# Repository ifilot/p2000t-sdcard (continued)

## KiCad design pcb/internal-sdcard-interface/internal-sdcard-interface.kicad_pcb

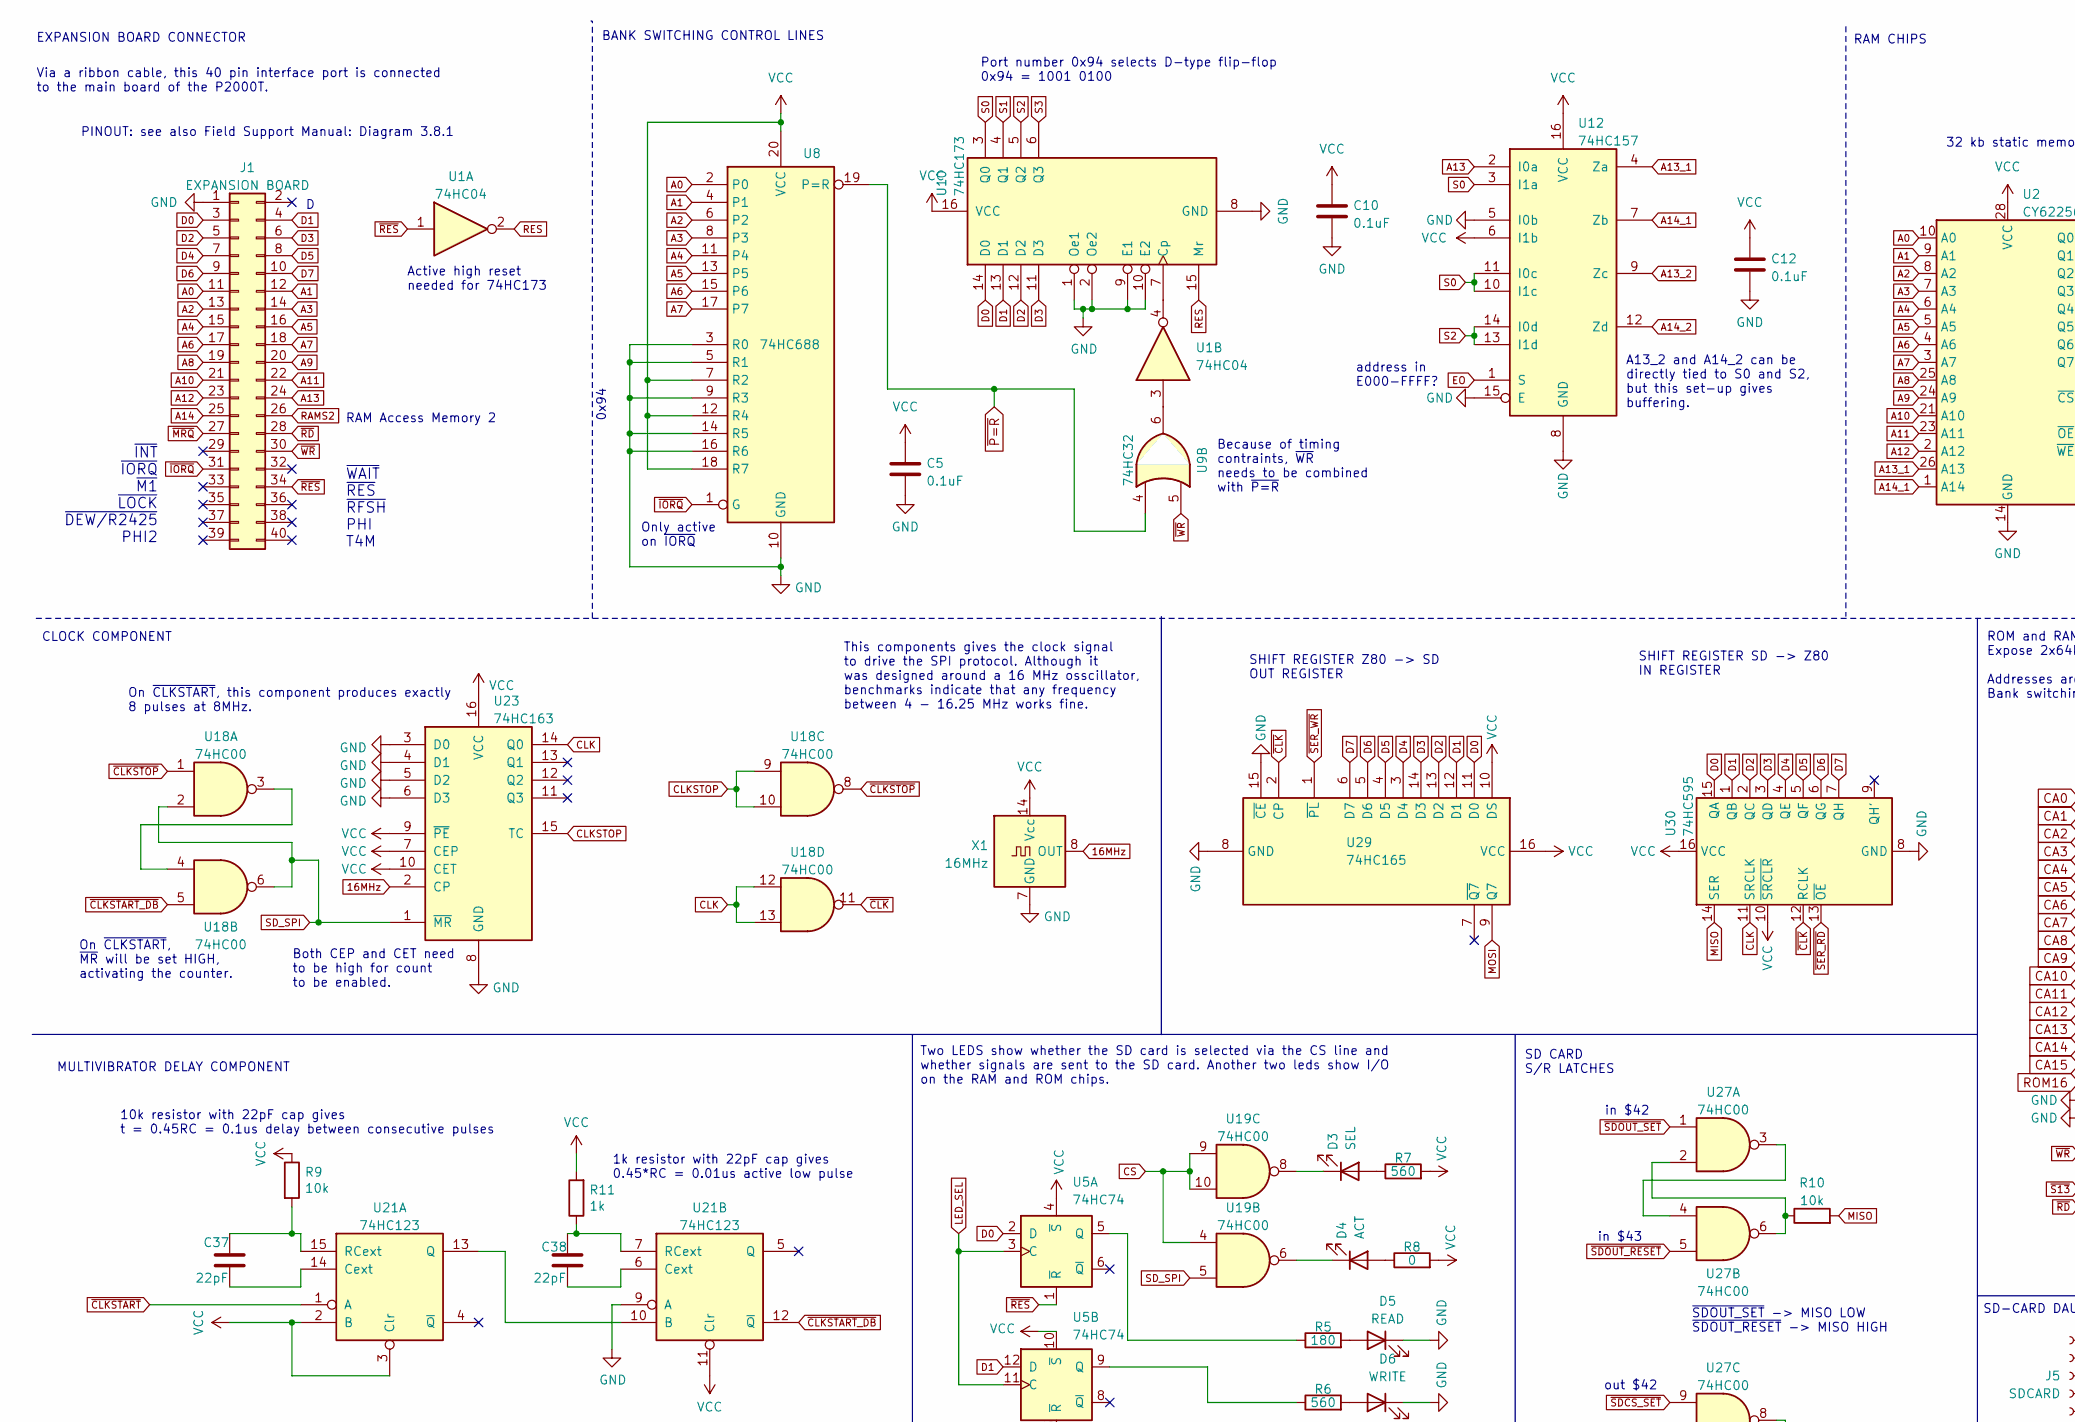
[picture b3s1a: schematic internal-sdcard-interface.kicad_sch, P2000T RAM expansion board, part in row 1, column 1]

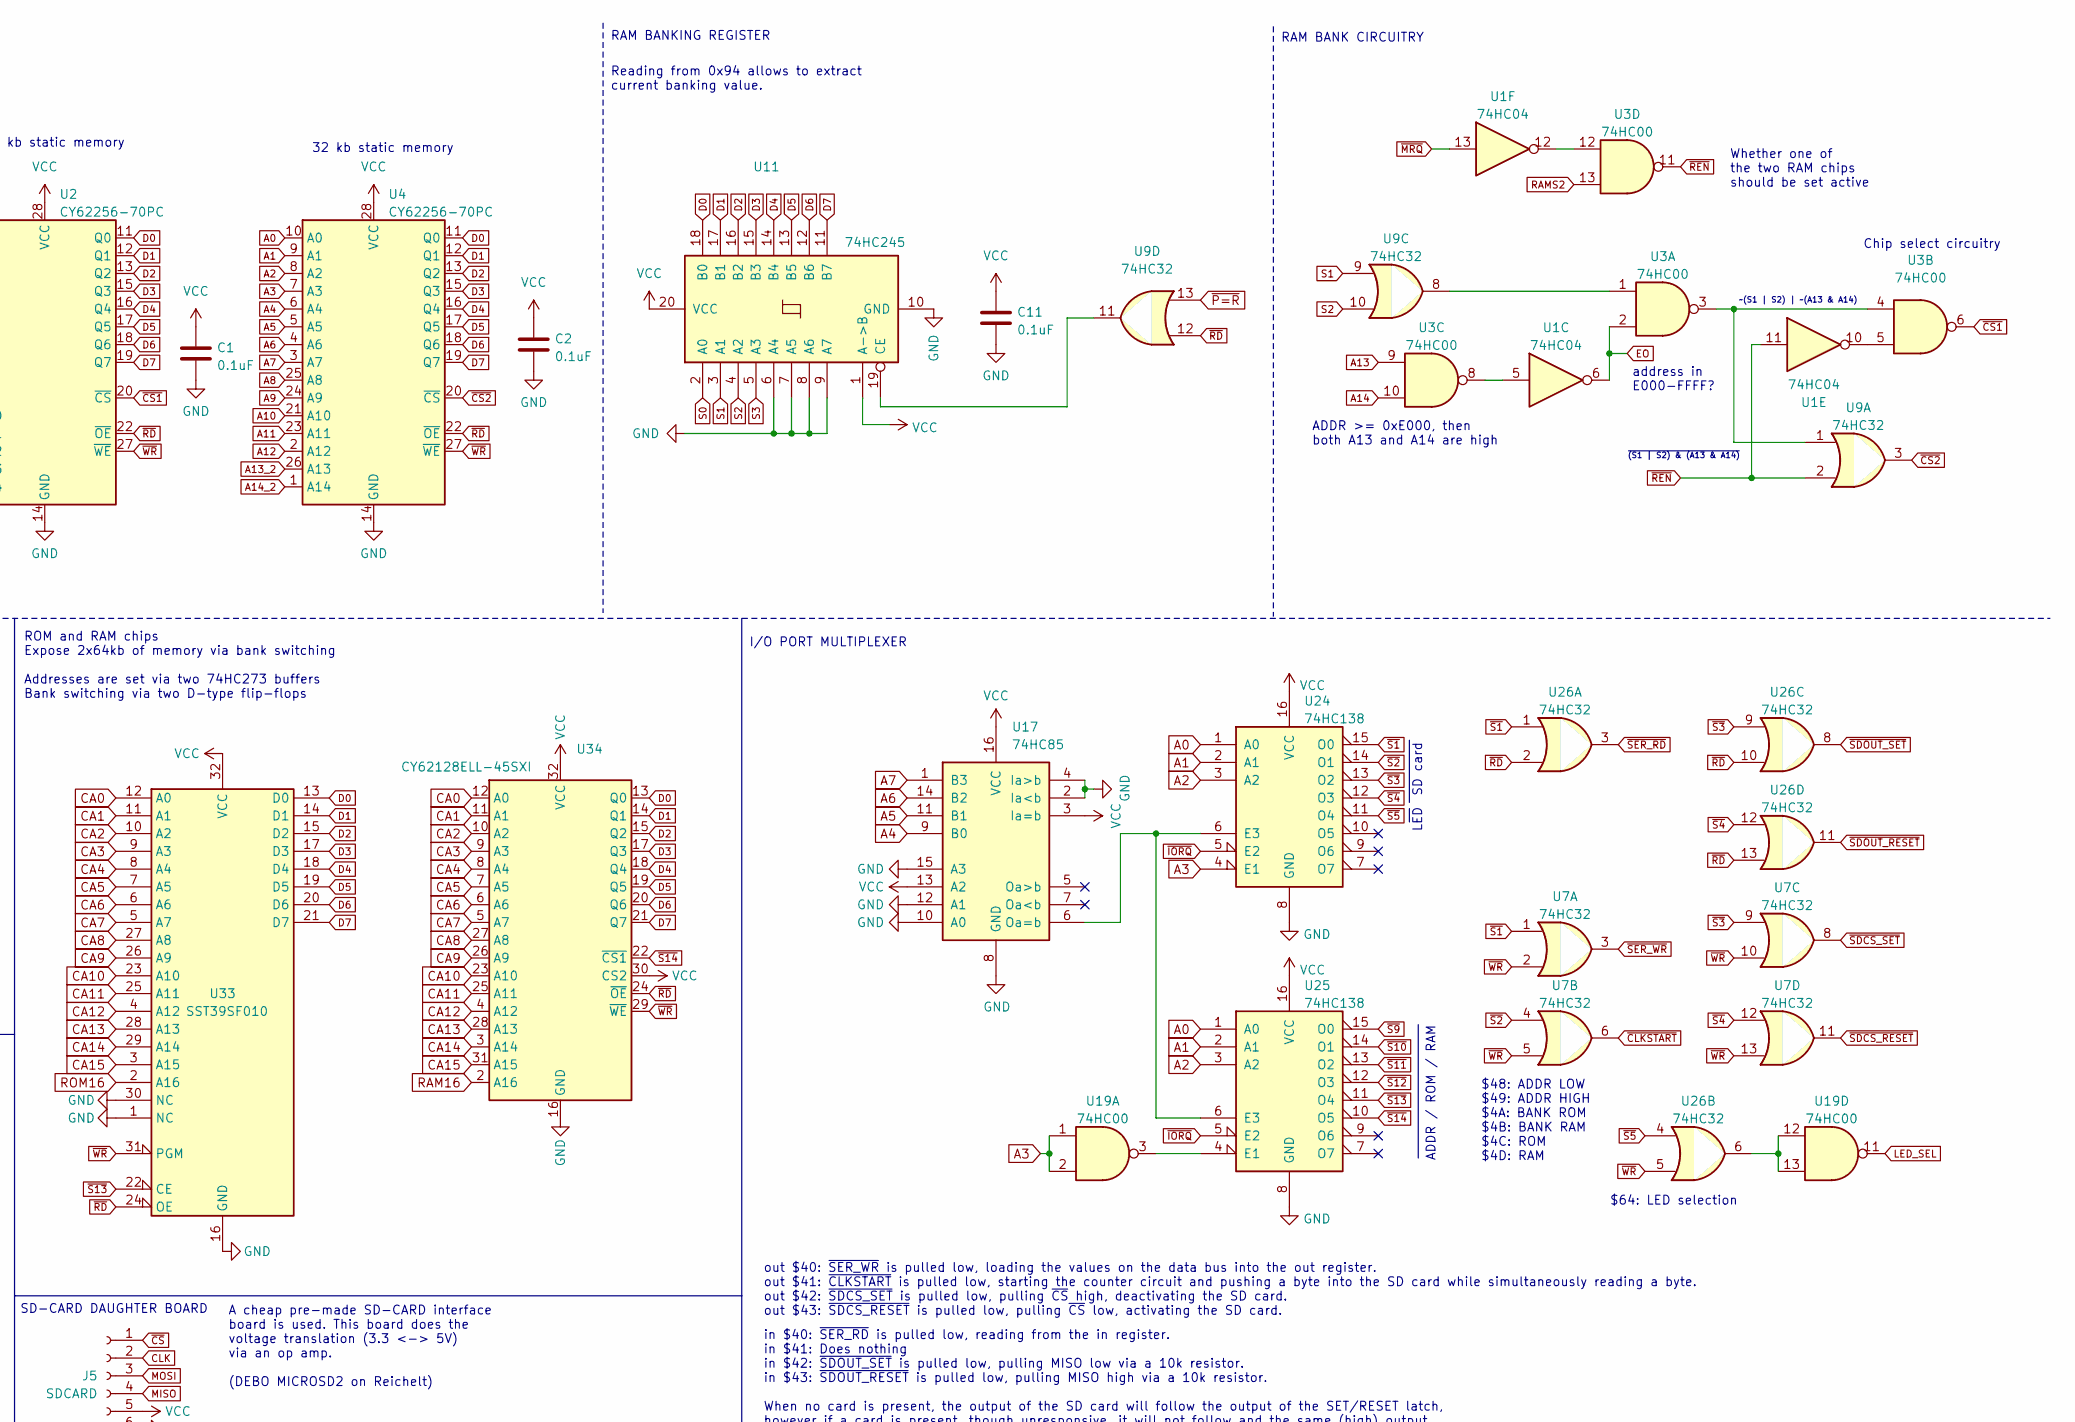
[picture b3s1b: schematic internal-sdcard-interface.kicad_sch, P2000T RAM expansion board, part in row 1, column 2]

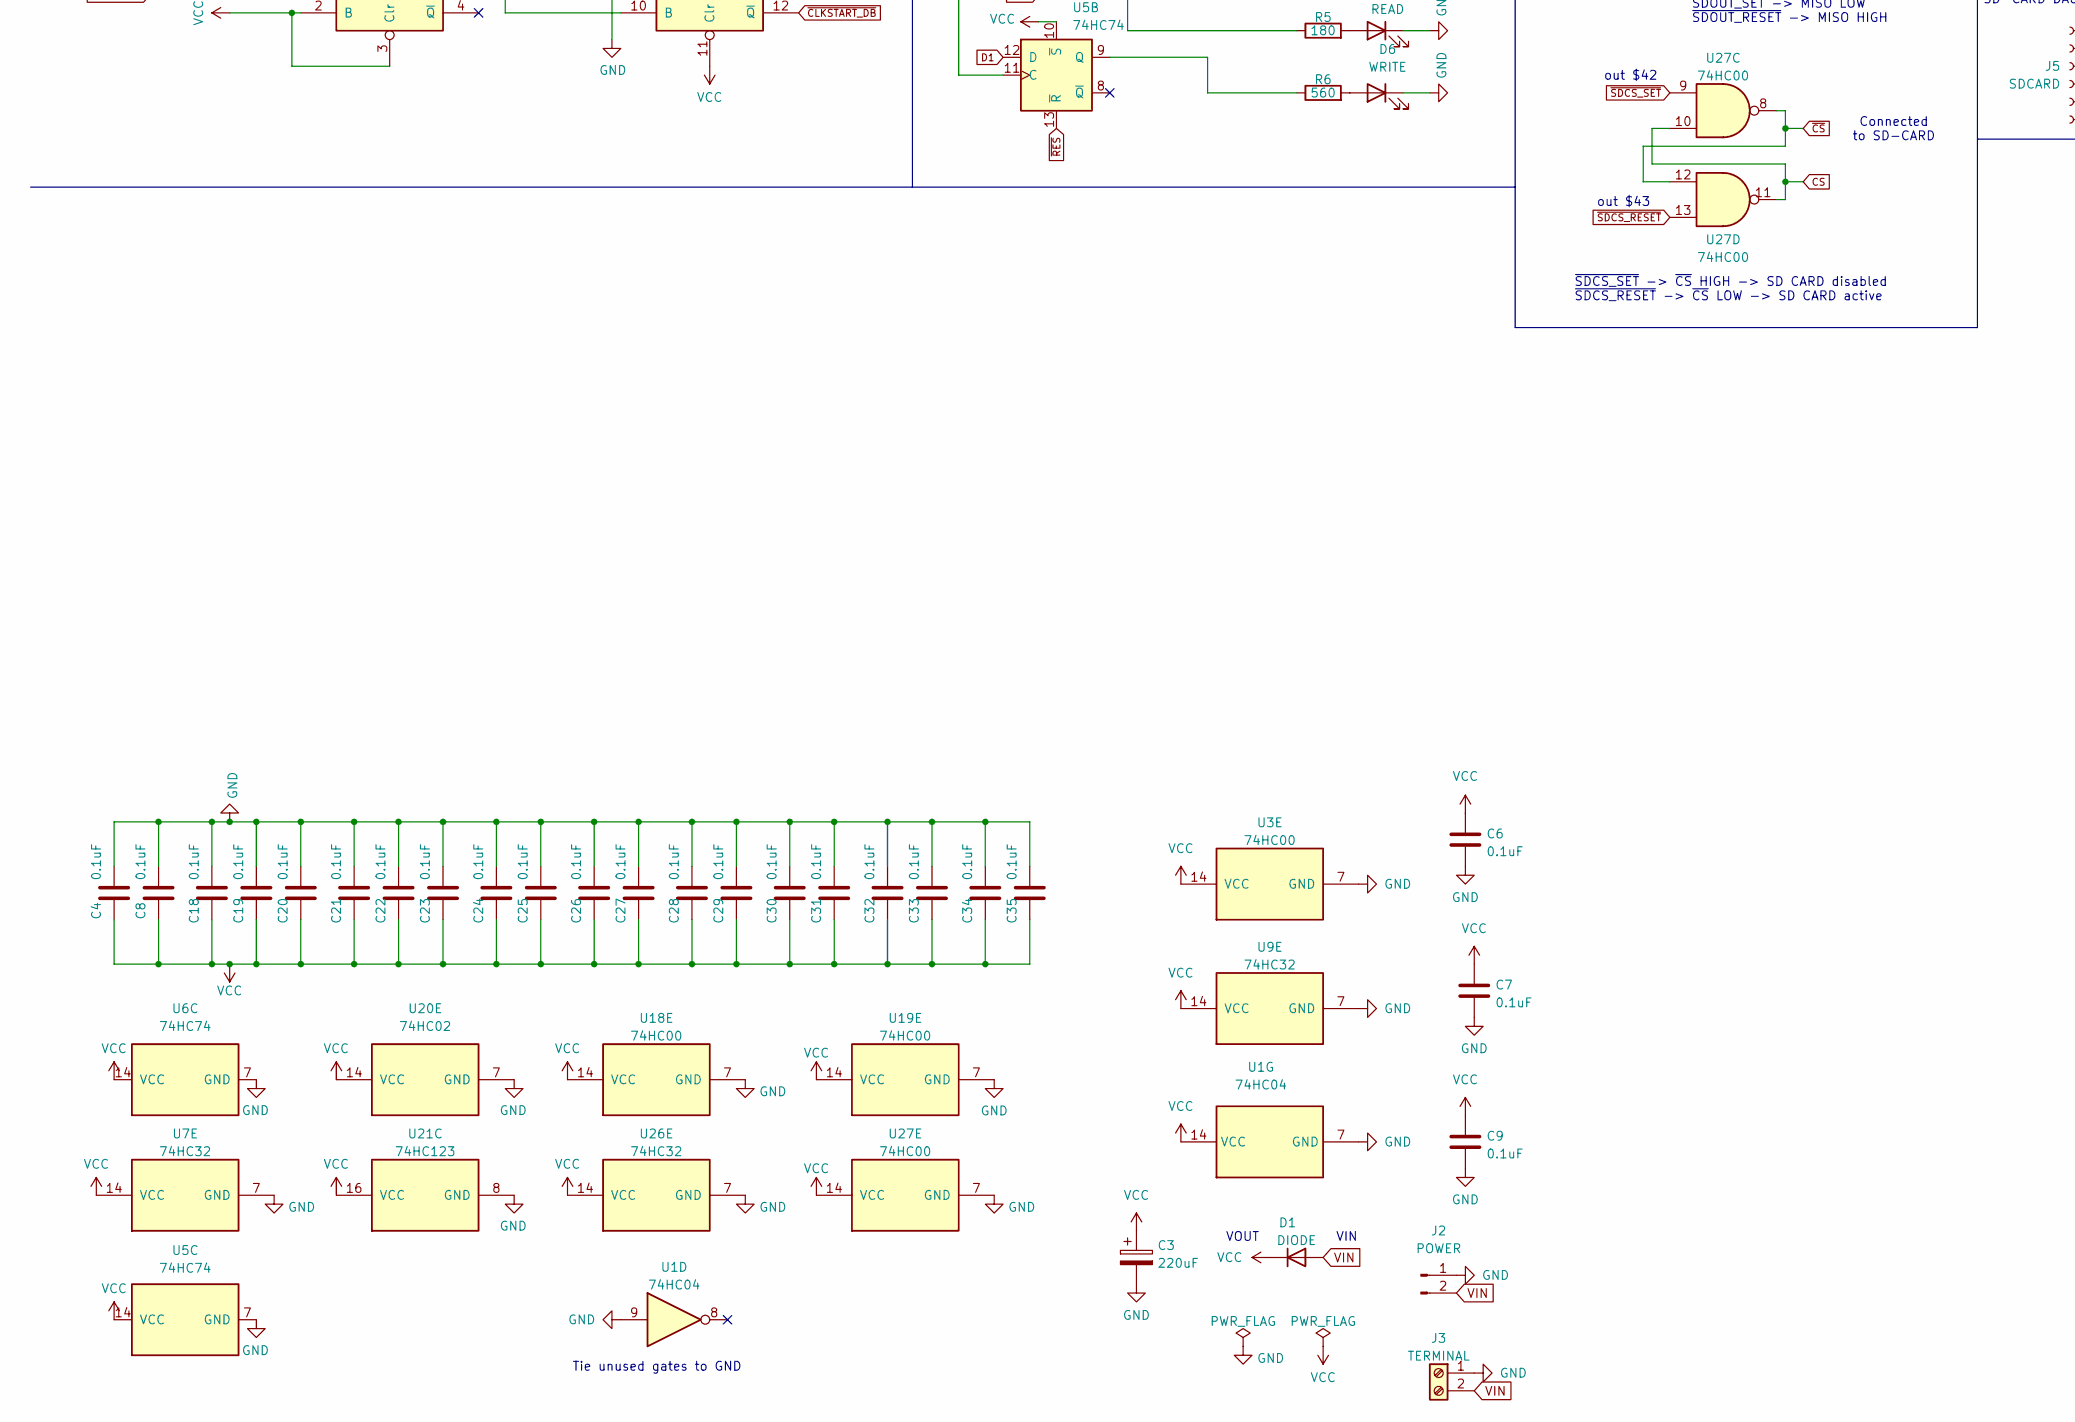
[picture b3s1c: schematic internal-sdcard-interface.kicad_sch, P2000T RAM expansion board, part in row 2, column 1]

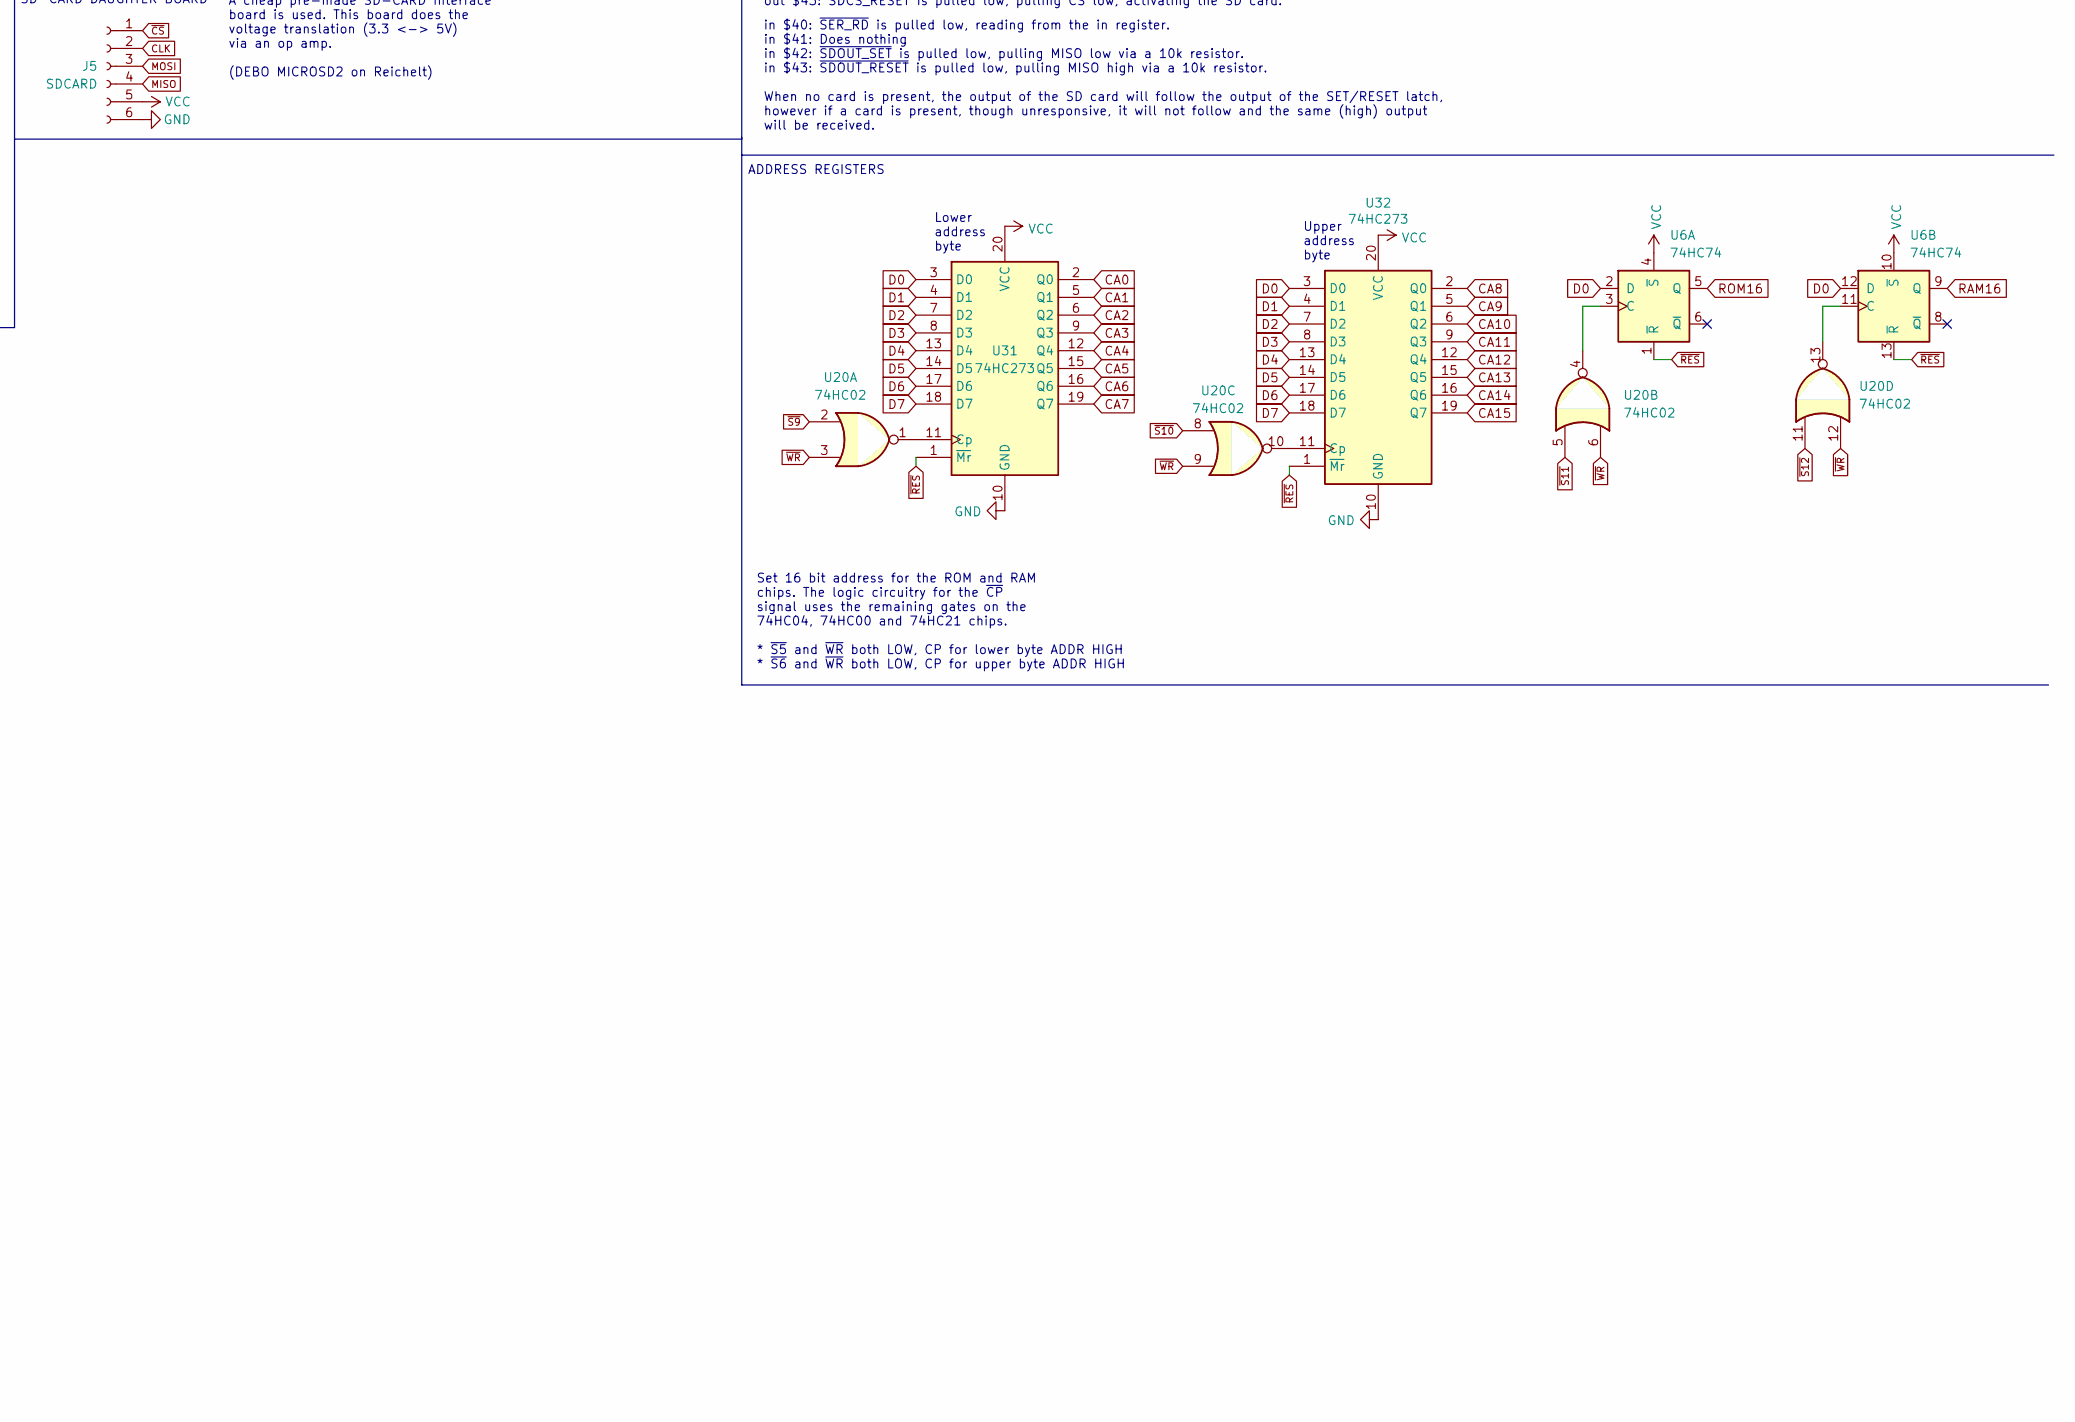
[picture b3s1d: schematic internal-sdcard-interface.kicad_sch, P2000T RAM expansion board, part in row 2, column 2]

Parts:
C1, C2, C5, C6, C7, C9, C10, C11, C12: 0.1uF; C_Disc_D5.0mm_W2.5mm_P5.00mm
C3: 220uF; CP_Radial_D6.3mm_P2.50mm
C4, C8, C18, C19, C20, C21, C22, C23, C24, C25, C26, C27, C28, C29, C30, C31, C32, C33, C34, C35: 0.1uF; C_Disc_D5.0mm_W2.5mm_P5.00mm; LCSC Part # C126469
C37, C38: 22pF; C_Disc_D5.0mm_W2.5mm_P5.00mm; LCSC Part # C525286
D1: DIODE; D_DO-35_SOD27_P7.62mm_Horizontal
D3: SEL; LED_D5.0mm
D4: ACT; LED_D5.0mm
D5: READ; LED_D5.0mm
D6: WRITE; LED_D5.0mm
J1: EXPANSION BOARD; IDC-Header_2x20_P2.54mm_Vertical
J2: POWER; PinHeader_1x02_P2.54mm_Vertical
J3: TERMINAL; TerminalBlock_bornier-2_P5.08mm
J5: SDCARD; sdcard-socket
R5: 180; R_Axial_DIN0207_L6.3mm_D2.5mm_P7.62mm_Horizontal; LCSC Part # C429158
R6, R7: 560; R_Axial_DIN0207_L6.3mm_D2.5mm_P7.62mm_Horizontal; LCSC Part # C429158
R8: 0; R_Axial_DIN0207_L6.3mm_D2.5mm_P7.62mm_Horizontal; LCSC Part # C431818
R9, R10: 10k; R_Axial_DIN0207_L6.3mm_D2.5mm_P7.62mm_Horizontal; LCSC Part # C5159708
R11: 1k; R_Axial_DIN0207_L6.3mm_D2.5mm_P7.62mm_Horizontal; LCSC Part # C5123594
U1: 74HC04; DIP-14_W7.62mm_Socket
U2, U4: CY62256-70PC; DIP-28_W15.24mm_Socket
U3: 74HC00; DIP-14_W7.62mm_Socket
U5, U6: 74HC74; DIP-14_W7.62mm_Socket; LCSC Part # C27597
U7, U26: 74HC32; DIP-14_W7.62mm_Socket; LCSC Part # C5632
U8: 74HC688; DIP-20_W7.62mm_Socket
U9: 74HC32; DIP-14_W7.62mm_Socket
U10: 74HC173; DIP-16_W7.62mm_Socket
U11: 74HC245; DIP-20_W7.62mm_Socket
U12: 74HC157; DIP-16_W7.62mm_Socket
U17: 74HC85; DIP-16_W7.62mm_Socket; LCSC Part # C5953
U18, U19, U27: 74HC00; DIP-14_W7.62mm_Socket; LCSC Part # C699445
U20: 74HC02; DIP-14_W7.62mm_Socket; LCSC Part # C5588
U21: 74HC123; DIP-16_W7.62mm_Socket; LCSC Part # C5597
U23: 74HC163; DIP-16_W7.62mm_Socket; LCSC Part # C338758
U24, U25: 74HC138; DIP-16_W7.62mm_Socket; LCSC Part # C5602
U29: 74HC165; DIP-16_W7.62mm_Socket; LCSC Part # C5613
U30: 74HC595; DIP-16_W7.62mm_Socket; LCSC Part # C5947
U31, U32: 74HC273; DIP-20_W7.62mm_Socket; LCSC Part # C131486
U33: SST39SF010; PLCC-32_THT-Socket
U34: CY62128ELL-45SXI; SSOP-32_11.305x20.495mm_P1.27mm; LCSC Part # C2840304
X1: 16MHz; Oscillator_DIP-14

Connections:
16MHz: U23.2 (CP), X1.8 (OUT)
A0: J1.11, U2.10 (A0), U4.10 (A0), U8.2 (P0), U24.1 (A0), U25.1 (A0)
A1: J1.12, U2.9 (A1), U4.9 (A1), U8.4 (P1), U24.2 (A1), U25.2 (A1)
A2: J1.13, U2.8 (A2), U4.8 (A2), U8.6 (P2), U24.3 (A2), U25.3 (A2)
A3: J1.14, U2.7 (A3), U4.7 (A3), U8.8 (P3), U19.1, U19.2, U24.4 (E1)
A4: J1.15, U2.6 (A4), U4.6 (A4), U8.11 (P4), U17.9 (B0)
A5: J1.16, U2.5 (A5), U4.5 (A5), U8.13 (P5), U17.11 (B1)
A6: J1.17, U2.4 (A6), U4.4 (A6), U8.15 (P6), U17.14 (B2)
A7: J1.18, U2.3 (A7), U4.3 (A7), U8.17 (P7), U17.1 (B3)
A8: J1.19, U2.25 (A8), U4.25 (A8)
A9: J1.20, U2.24 (A9), U4.24 (A9)
A10: J1.21, U2.21 (A10), U4.21 (A10)
A11: J1.22, U2.23 (A11), U4.23 (A11)
A12: J1.23, U2.2 (A12), U4.2 (A12)
A13: J1.24, U3.9, U12.2 (I0a)
A13_1: U2.26 (A13), U12.4 (Za)
A13_2: U4.26 (A13), U12.9 (Zc)
A14: J1.25, U3.10
A14_1: U2.1 (A14), U12.7 (Zb)
A14_2: U4.1 (A14), U12.12 (Zd)
CA0: U31.2 (Q0), U33.12 (A0), U34.12 (A0)
CA1: U31.5 (Q1), U33.11 (A1), U34.11 (A1)
CA2: U31.6 (Q2), U33.10 (A2), U34.10 (A2)
CA3: U31.9 (Q3), U33.9 (A3), U34.9 (A3)
CA4: U31.12 (Q4), U33.8 (A4), U34.8 (A4)
CA5: U31.15 (Q5), U33.7 (A5), U34.7 (A5)
CA6: U31.16 (Q6), U33.6 (A6), U34.6 (A6)
CA7: U31.19 (Q7), U33.5 (A7), U34.5 (A7)
CA8: U32.2 (Q0), U33.27 (A8), U34.27 (A8)
CA9: U32.5 (Q1), U33.26 (A9), U34.26 (A9)
CA10: U32.6 (Q2), U33.23 (A10), U34.23 (A10)
CA11: U32.9 (Q3), U33.25 (A11), U34.25 (A11)
CA12: U32.12 (Q4), U33.4 (A12), U34.4 (A12)
CA13: U32.15 (Q5), U33.28 (A13), U34.28 (A13)
CA14: U32.16 (Q6), U33.29 (A14), U34.3 (A14)
CA15: U32.19 (Q7), U33.3 (A15), U34.31 (A15)
CLK: J5.2, U18.12, U18.13, U23.14 (Q0), U30.11 (SRCLK)
CLKSTOP: U18.9, U18.10, U23.15 (TC)
CS: U19.4, U19.9, U19.10, U27.10, U27.11
D0: J1.3, U2.11 (Q0), U4.11 (Q0), U5.2 (D), U6.2 (D), U6.12 (D), U10.14 (D0), U11.18 (B0), U29.11 (D0), U30.15 (QA), U31.3 (D0), U32.3 (D0), U33.13 (D0), U34.13 (Q0)
D1: J1.4, U2.12 (Q1), U4.12 (Q1), U5.12 (D), U10.13 (D1), U11.17 (B1), U29.12 (D1), U30.1 (QB), U31.4 (D1), U32.4 (D1), U33.14 (D1), U34.14 (Q1)
D2: J1.5, U2.13 (Q2), U4.13 (Q2), U10.12 (D2), U11.16 (B2), U29.13 (D2), U30.2 (QC), U31.7 (D2), U32.7 (D2), U33.15 (D2), U34.15 (Q2)
D3: J1.6, U2.15 (Q3), U4.15 (Q3), U10.11 (D3), U11.15 (B3), U29.14 (D3), U30.3 (QD), U31.8 (D3), U32.8 (D3), U33.17 (D3), U34.17 (Q3)
D4: J1.7, U2.16 (Q4), U4.16 (Q4), U11.14 (B4), U29.3 (D4), U30.4 (QE), U31.13 (D4), U32.13 (D4), U33.18 (D4), U34.18 (Q4)
D5: J1.8, U2.17 (Q5), U4.17 (Q5), U11.13 (B5), U29.4 (D5), U30.5 (QF), U31.14 (D5), U32.14 (D5), U33.19 (D5), U34.19 (Q5)
D6: J1.9, U2.18 (Q6), U4.18 (Q6), U11.12 (B6), U29.5 (D6), U30.6 (QG), U31.17 (D6), U32.17 (D6), U33.20 (D6), U34.20 (Q6)
D7: J1.10, U2.19 (Q7), U4.19 (Q7), U11.11 (B7), U29.6 (D7), U30.7 (QH), U31.18 (D7), U32.18 (D7), U33.21 (D7), U34.21 (Q7)
EO: U1.6, U3.2, U12.1 (S)
GND: C1.2, C2.2, C3.2, C4.2, C5.2, C6.2, C7.2, C8.2, C9.2, C10.2, C11.2, C12.2, C18.2, C19.2, C20.2, C21.2, C22.2, C23.2, C24.2, C25.2, C26.2, C27.2, C28.2, C29.2, C30.2, C31.2, C32.2, C33.2, C34.2, C35.2, D5.1 (K), D6.1 (K), J1.1, J2.1, J3.1, J5.6, U1.7 (GND), U1.9, U2.14 (GND), U3.7 (GND), U4.14 (GND), U5.7 (GND), U6.7 (GND), U7.7 (GND), U8.3 (R0), U8.5 (R1), U8.9 (R3), U8.10 (GND), U8.14 (R5), U8.16 (R6), U9.7 (GND), U10.1 (Oe1), U10.2 (Oe2), U10.8 (GND), U10.9 (E1), U10.10 (E2), U11.6 (A4), U11.7 (A5), U11.8 (A6), U11.9 (A7), U11.10 (GND), U12.5 (I0b), U12.8 (GND), U12.15 (E), U17.2 (Ia<b), U17.4 (Ia>b), U17.8 (GND), U17.10 (A0), U17.12 (A1), U17.15 (A3), U18.7 (GND), U19.7 (GND), U20.7 (GND), U21.8 (GND), U21.9 (A), U23.3 (D0), U23.4 (D1), U23.5 (D2), U23.6 (D3), U23.8 (GND), U24.8 (GND), U25.8 (GND), U26.7 (GND), U27.7 (GND), U29.8 (GND), U29.15 (~CE), U30.8 (GND), U31.10 (GND), U32.10 (GND), U33.1 (NC), U33.16 (GND), U33.30 (NC), U34.16 (GND), X1.7 (GND)
LED_SEL: U5.3 (C), U5.11 (C), U19.11
MISO: J5.4, R10.2, U30.14 (SER)
MOSI: J5.3, U29.9 (Q7)
unnamed: D3.2 (A), R7.1
unnamed: D3.1 (K), U19.8
unnamed: D4.2 (A), R8.1
unnamed: D4.1 (K), U19.6
unnamed: D5.2 (A), R5.2
unnamed: D6.2 (A), R6.2
unnamed: R10.1, U27.2, U27.6
unnamed: U1.3, U9.6
unnamed: U1.5, U3.8
unnamed: U1.10, U3.5
unnamed: U1.12, U3.12
unnamed: U3.1, U9.8
unnamed: U3.3, U3.4, U9.1
unnamed: R5.1, U5.5 (Q)
unnamed: R6.1, U5.9 (Q)
unnamed: U6.3 (C), U20.4
unnamed: U6.11 (C), U20.13
unnamed: U1.4, U10.7 (Cp)
unnamed: U9.11, U11.19 (CE)
unnamed: U17.6 (Oa=b), U24.6 (E3), U25.6 (E3)
unnamed: U18.3, U18.4
unnamed: U19.12, U19.13, U26.6
unnamed: C37.1, U21.14 (Cext)
unnamed: U21.10 (B), U21.13 (Q)
unnamed: C37.2, R9.2, U21.15 (RCext)
unnamed: C38.1, U21.6 (Cext)
unnamed: C38.2, R11.1, U21.7 (RCext)
unnamed: U19.3, U25.4 (E1)
unnamed: U27.3, U27.4
unnamed: U20.1, U31.11 (Cp)
unnamed: U20.10, U32.11 (Cp)
RAM16: U6.9 (Q), U34.2 (A16)
RAMS2: J1.26, U3.13
RES: U1.2, U10.15 (Mr)
ROM16: U6.5 (Q), U33.2 (A16)
S0: U10.3 (Q0), U11.2 (A0), U12.3 (I1a), U12.10 (I1c), U12.11 (I0c)
S1: U9.9, U10.4 (Q1), U11.3 (A1)
S2: U9.10, U10.5 (Q2), U11.4 (A2), U12.13 (I1d), U12.14 (I0d)
S3: U10.6 (Q3), U11.5 (A3)
SD_SPI: U18.2, U18.6, U19.5, U23.1 (~MR)
VCC: C1.1, C2.1, C3.1, C4.1, C5.1, C6.1, C7.1, C8.1, C9.1, C10.1, C11.1, C12.1, C18.1, C19.1, C20.1, C21.1, C22.1, C23.1, C24.1, C25.1, C26.1, C27.1, C28.1, C29.1, C30.1, C31.1, C32.1, C33.1, C34.1, C35.1, D1.1 (K), J5.5, R7.2, R8.2, R9.1, R11.2, U1.14 (VCC), U2.28 (VCC), U3.14 (VCC), U4.28 (VCC), U5.4 (~S), U5.10 (~S), U5.14 (VCC), U6.4 (~S), U6.10 (~S), U6.14 (VCC), U7.14 (VCC), U8.7 (R2), U8.12 (R4), U8.18 (R7), U8.20 (VCC), U9.14 (VCC), U10.16 (VCC), U11.1 (A->B), U11.20 (VCC), U12.6 (I1b), U12.16 (VCC), U17.3 (Ia=b), U17.13 (A2), U17.16 (VCC), U18.14 (VCC), U19.14 (VCC), U20.14 (VCC), U21.2 (B), U21.3 (Clr), U21.11 (Clr), U21.16 (VCC), U23.7 (CEP), U23.9 (~PE), U23.10 (CET), U23.16 (VCC), U24.16 (VCC), U25.16 (VCC), U26.14 (VCC), U27.14 (VCC), U29.10 (DS), U29.16 (VCC), U30.10 (~SRCLR), U30.16 (VCC), U31.20 (VCC), U32.20 (VCC), U33.32 (VCC), U34.30 (CS2), U34.32 (VCC), X1.14 (Vcc)
VIN: D1.2 (A), J2.2, J3.2
~CLKSTART_DB: U18.5, U21.12 (~Q)
~CLKSTART: U7.6, U21.1 (A)
~CLKSTOP: U18.1, U18.8
~CLK: U18.11, U29.2 (CP), U30.12 (RCLK)
~CS1: U2.20 (~CS), U3.6
~CS2: U4.20 (~CS), U9.3
~CS: J5.1, U27.8, U27.12
~IORQ: J1.31, U8.1 (G), U24.5 (E2), U25.5 (E2)
~MRQ: J1.27, U1.13
~P=R: U8.19 (P=R), U9.4, U9.13
~RD: J1.28, U2.22 (~OE), U4.22 (~OE), U9.12, U26.2, U26.10, U26.13, U33.24 (OE), U34.24 (~OE)
~REN: U1.11, U3.11, U9.2
~RES: J1.34, U1.1, U5.1 (~R), U5.13 (~R), U6.1 (~R), U6.13 (~R), U31.1 (~Mr), U32.1 (~Mr)
~S1: U7.1, U24.15 (O0), U26.1
~S2: U7.4, U24.14 (O1)
~S3: U7.9, U24.13 (O2), U26.9
~S4: U7.12, U24.12 (O3), U26.12
~S5: U24.11 (O4), U26.4
~S9: U20.2, U25.15 (O0)
~S10: U20.8, U25.14 (O1)
~S11: U20.5, U25.13 (O2)
~S12: U20.11, U25.12 (O3)
~S13: U25.11 (O4), U33.22 (CE)
~S14: U25.10 (O5), U34.22 (~CS1)
~SDCS_RESET: U7.11, U27.13
~SDCS_SET: U7.8, U27.9
~SDOUT_RESET: U26.11, U27.5
~SDOUT_SET: U26.8, U27.1
~SER_RD: U26.3, U30.13 (~OE)
~SER_WR: U7.3, U29.1 (~PL)
~WR: J1.30, U2.27 (~WE), U4.27 (~WE), U7.2, U7.5, U7.10, U7.13, U9.5, U20.3, U20.6, U20.9, U20.12, U26.5, U33.31 (PGM), U34.29 (~WE)

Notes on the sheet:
Lower address byte
SD CARD S/R LATCHES
Upper address byte
Reading from 0x94 allows to extract current banking value.
Via a ribbon cable, this 40 pin interface port is connected to the main board of the P2000T.
32 kb static memory
EXPANSION BOARD CONNECTOR
RAM Access Memory 2
1k resistor with 22pF cap gives 0.45*RC = 0.01us active low pulse
Whether one of the two RAM chips should be set active
Two LEDS show whether the SD card is selected via the CS line and whether signals are sent to the SD card. Another two leds show I/O on the RAM and ROM chips.
This components gives the clock signal to drive the SPI protocol. Although it was designed around a 16 MHz osscillator, benchmarks indicate that any frequency between 4 - 16.25 MHz works fine.
out $40: ~{SER_WR} is pulled low, loading the values on the data bus into the out register. out $41: ~{CLKSTART} is pulled low, starting the counter circuit and pushing a byte into the SD card while simultaneously reading a byte. out $42: ~{SDCS_SET} is pulled low, pulling ~{CS} high, deactivating 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
A cheap pre-made SD-CARD interface board is used. This board does the voltage translation (3.3 <-> 5V) via an op amp. (DEBO MICROSD2 on Reichelt)
0x94
~{INT} ~{IORQ} ~{M1} ~{LOCK} ~{DEW/R2425} PHI2
ROM and RAM chips Expose 2x64kb of memory via bank switching Addresses are set via two 74HC273 buffers Bank switching via two D-type flip-flops
~{SDCS_SET} -> ~{CS} HIGH -> SD CARD disabled ~{SDCS_RESET} -> ~{CS} LOW -> SD CARD active
out $42
RAM BANKING REGISTER
I/O PORT MULTIPLEXER
~{(S1 | S2) & (A13 & A14)}
~{SDOUT_SET} -> MISO LOW ~{SDOUT_RESET} -> MISO HIGH
Tie unused gates to GND
SD card
RAM BANK CIRCUITRY
On ~{CLKSTART}, this component produces exactly 8 pulses at 8MHz.
Connected to SD-CARD
Active high reset needed for 74HC173
Only active on ~{IORQ}
Because of timing contraints, ~{WR} needs to be combined with ~{P=R}
address in E000-FFFF?
out $43
ADDR / ROM / RAM
10k resistor with 22pF cap gives t = 0.45RC = 0.1us delay between consecutive pulses
Both CEP and CET need to be high for count to be enabled.
SHIFT REGISTER SD -> Z80 IN REGISTER
On ~{CLKSTART}, ~{MR} will be set HIGH, activating the counter.
ADDR >= 0xE000, then both A13 and A14 are high
MULTIVIBRATOR DELAY COMPONENT

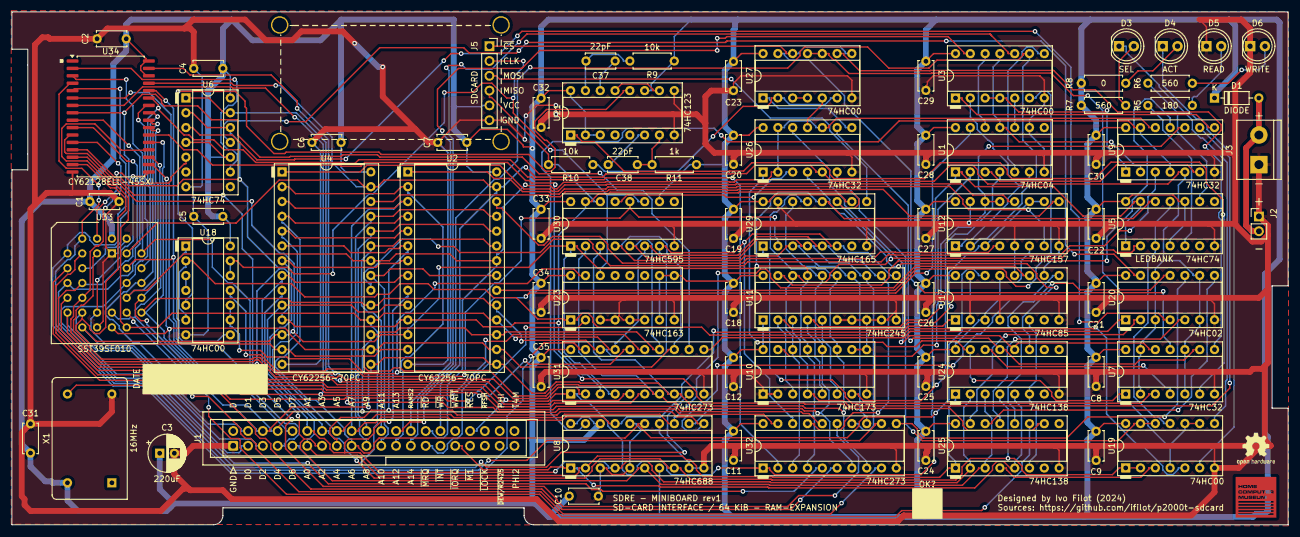
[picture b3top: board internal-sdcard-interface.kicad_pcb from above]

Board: 2 copper layers, 219.0 x 88.0 mm, 78 parts (0 on the bottom side), 125 nets.

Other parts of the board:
G001: LOGO; hcm_logo
